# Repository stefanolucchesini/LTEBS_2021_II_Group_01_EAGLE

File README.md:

# LTEBS_2021_II_Group_01_EAGLE

This is the first assignment of electronic technologies and biosensors LAB. 

We are group 1:
*Stefano Lucchesini
*Michele Civitavecchia

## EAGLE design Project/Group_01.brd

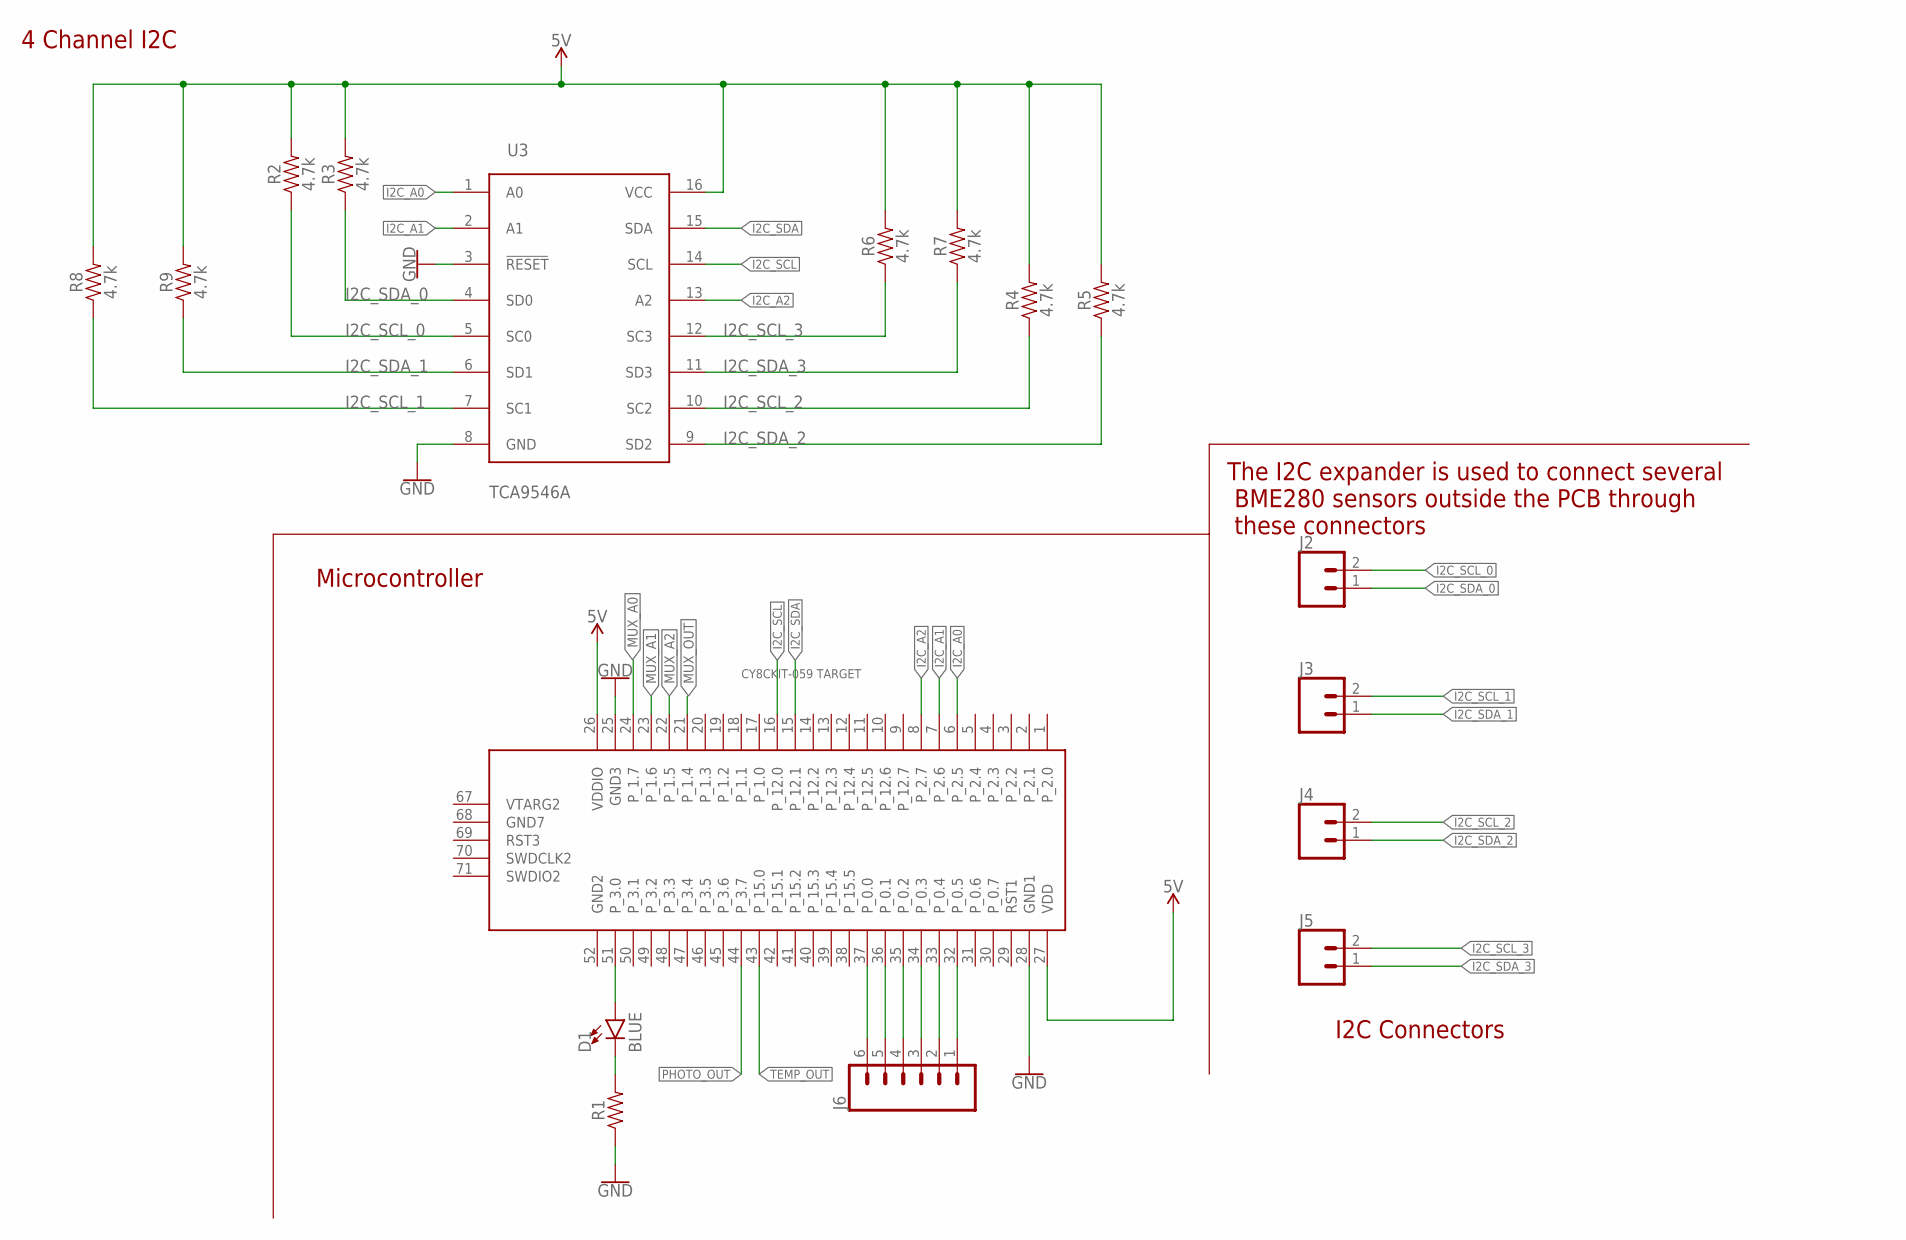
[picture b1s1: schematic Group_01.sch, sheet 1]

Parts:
D1: BLUE; LED-1206
J2, J3, J4, J5: CONN_02; 1X02
J6: CONN_06LOCK; 1X06_LOCK
R1: AXIAL-0.3
R2, R3, R4, R5, R6, R7, R8, R9: 4.7k; 0603
U3: TCA9546A; TSSOP16
U$2: CY8CKIT-059_TARGET

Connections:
5V: R2.2, R3.2, R4.2, R5.2, R6.2, R7.2, R8.2, R9.2, U3.16 (VCC), U$2.26 (VDDIO), U$2.27 (VDD); also elsewhere on the board
GND: R1.P$1 (1), U3.3 (!RESET!), U3.8 (GND), U$2.25 (GND3), U$2.28 (GND1); also elsewhere on the board
I2C_A0: U3.1 (A0), U$2.6 (P_2.5)
I2C_A1: U3.2 (A1), U$2.7 (P_2.6)
I2C_A2: U3.13 (A2), U$2.8 (P_2.7)
I2C_SCL: U3.14 (SCL), U$2.16 (P_12.0)
I2C_SCL_0: J2.2, R2.1, U3.5 (SC0)
I2C_SCL_1: J3.2, R8.1, U3.7 (SC1)
I2C_SCL_2: J4.2, R4.1, U3.10 (SC2)
I2C_SCL_3: J5.2, R6.1, U3.12 (SC3)
I2C_SDA: U3.15 (SDA), U$2.15 (P_12.1)
I2C_SDA_0: J2.1, R3.1, U3.4 (SD0)
I2C_SDA_1: J3.1, R9.1, U3.6 (SD1)
I2C_SDA_2: J4.1, R5.1, U3.9 (SD2)
I2C_SDA_3: J5.1, R7.1, U3.11 (SD3)
MUX_A0: U$2.24 (P_1.7); also elsewhere on the board
MUX_A1: U$2.23 (P_1.6); also elsewhere on the board
MUX_A2: U$2.22 (P_1.5); also elsewhere on the board
MUX_OUT: U$2.21 (P_1.4); also elsewhere on the board
unnamed: D1.A, U$2.51 (P_3.0)
unnamed: D1.C, R1.P$2 (2)
PHOTO_OUT: U$2.44 (P_3.7); also elsewhere on the board
P_0.0: J6.6, U$2.37 (P_0.0)
P_0.1: J6.5, U$2.36 (P_0.1)
P_0.2: J6.4, U$2.35 (P_0.2)
P_0.3: J6.3, U$2.34 (P_0.3)
P_0.4: J6.2, U$2.33 (P_0.4)
P_0.5: J6.1, U$2.32 (P_0.5)
TEMP_OUT: U$2.43 (P_15.0); also elsewhere on the board

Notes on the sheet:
I2C Connectors
The I2C expander is used to connect several BME280 sensors outside the PCB through these connectors
4 Channel I2C
Microcontroller

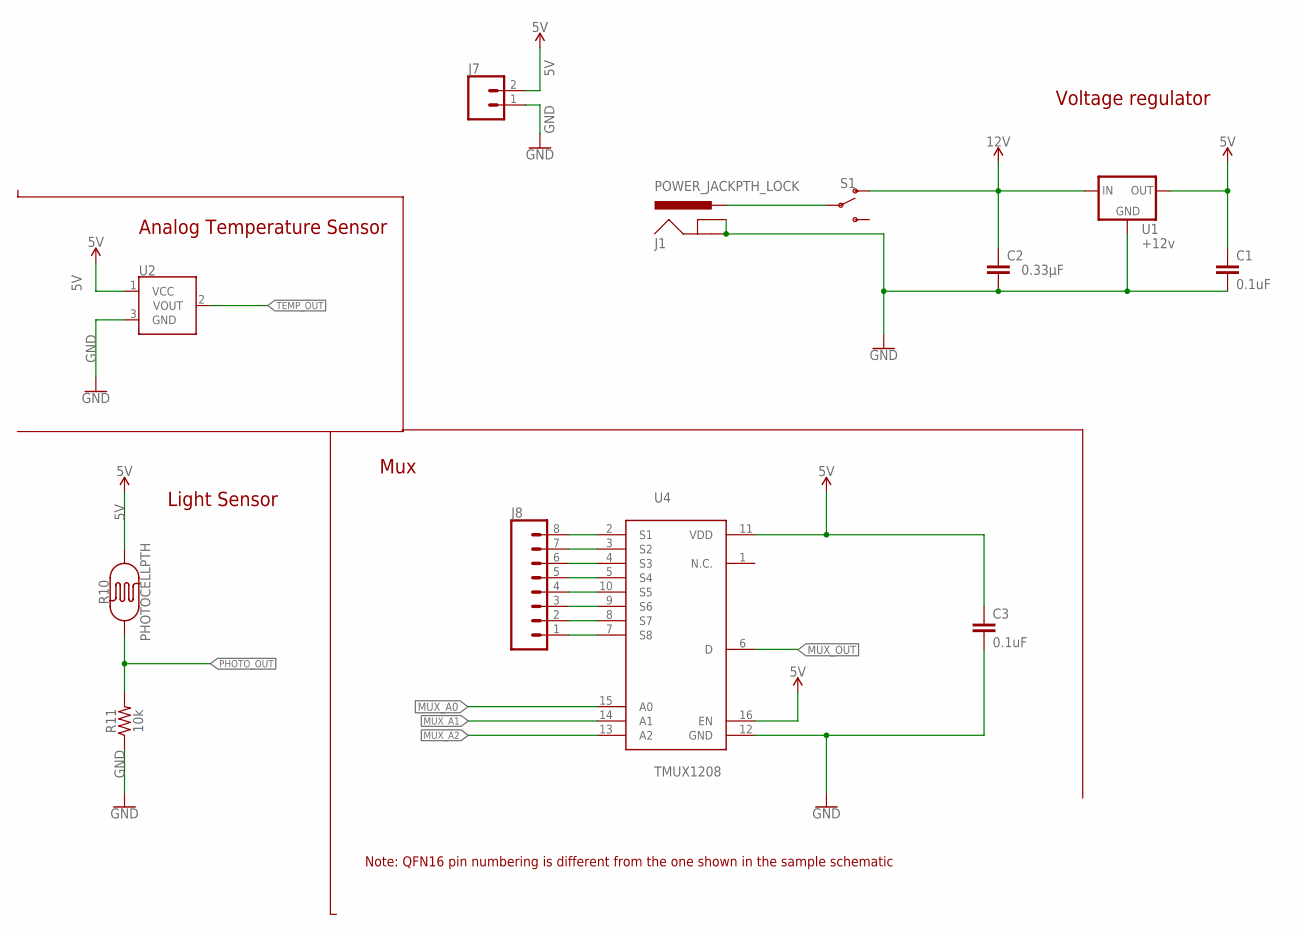
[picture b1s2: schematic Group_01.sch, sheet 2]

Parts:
C1, C3: 0.1uF; CAP-PTH-SMALL-KIT
C2: 0.33µF; 0805
J1: POWER_JACKPTH_LOCK; POWER_JACK_PTH_LOCK
J7: CONN_02; 1X02
J8: CONN_08LOCK; 1X08_LOCK
R10: PHOTOCELLPTH; PHOTOCELL
R11: 10k; 0603
S1: SWITCH-SPDT-PTH-11.6X4.0MM; SWITCH_SPDT_PTH_11.6X4.0MM
U1: +12v; TO-252
U2: TMP36GT9; TO-92
U4: TMUX1208; QFN16

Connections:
5V: C1.1, C3.1, J7.2, R10.2, U1.2 (OUT), U2.1 (VCC), U4.11 (VDD), U4.16 (EN); also elsewhere on the board
12V: C2.1, S1.1 (O), U1.1 (IN)
GND: C1.2, C2.2, C3.2, J1.GND, J1.GNDBREAK, J7.1, R11.1, U1.3 (GND), U2.3 (GND), U4.12 (GND); also elsewhere on the board
MUX_A0: U4.15 (A0); also elsewhere on the board
MUX_A1: U4.14 (A1); also elsewhere on the board
MUX_A2: U4.13 (A2); also elsewhere on the board
MUX_OUT: U4.6 (D); also elsewhere on the board
PHOTO_OUT: R10.1, R11.2; also elsewhere on the board
S1: J8.8, U4.2 (S1)
S2: J8.7, U4.3 (S2)
S3: J8.6, U4.4 (S3)
S4: J8.5, U4.5 (S4)
S5: J8.4, U4.10 (S5)
S6: J8.3, U4.9 (S6)
S7: J8.2, U4.8 (S7)
S8: J8.1, U4.7 (S8)
SWITCH: J1.PWR, S1.2
TEMP_OUT: U2.2 (VOUT); also elsewhere on the board

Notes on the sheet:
Analog Temperature Sensor
Light Sensor
Voltage regulator
Mux
Note: QFN16 pin numbering is different from the one shown in the sample schematic

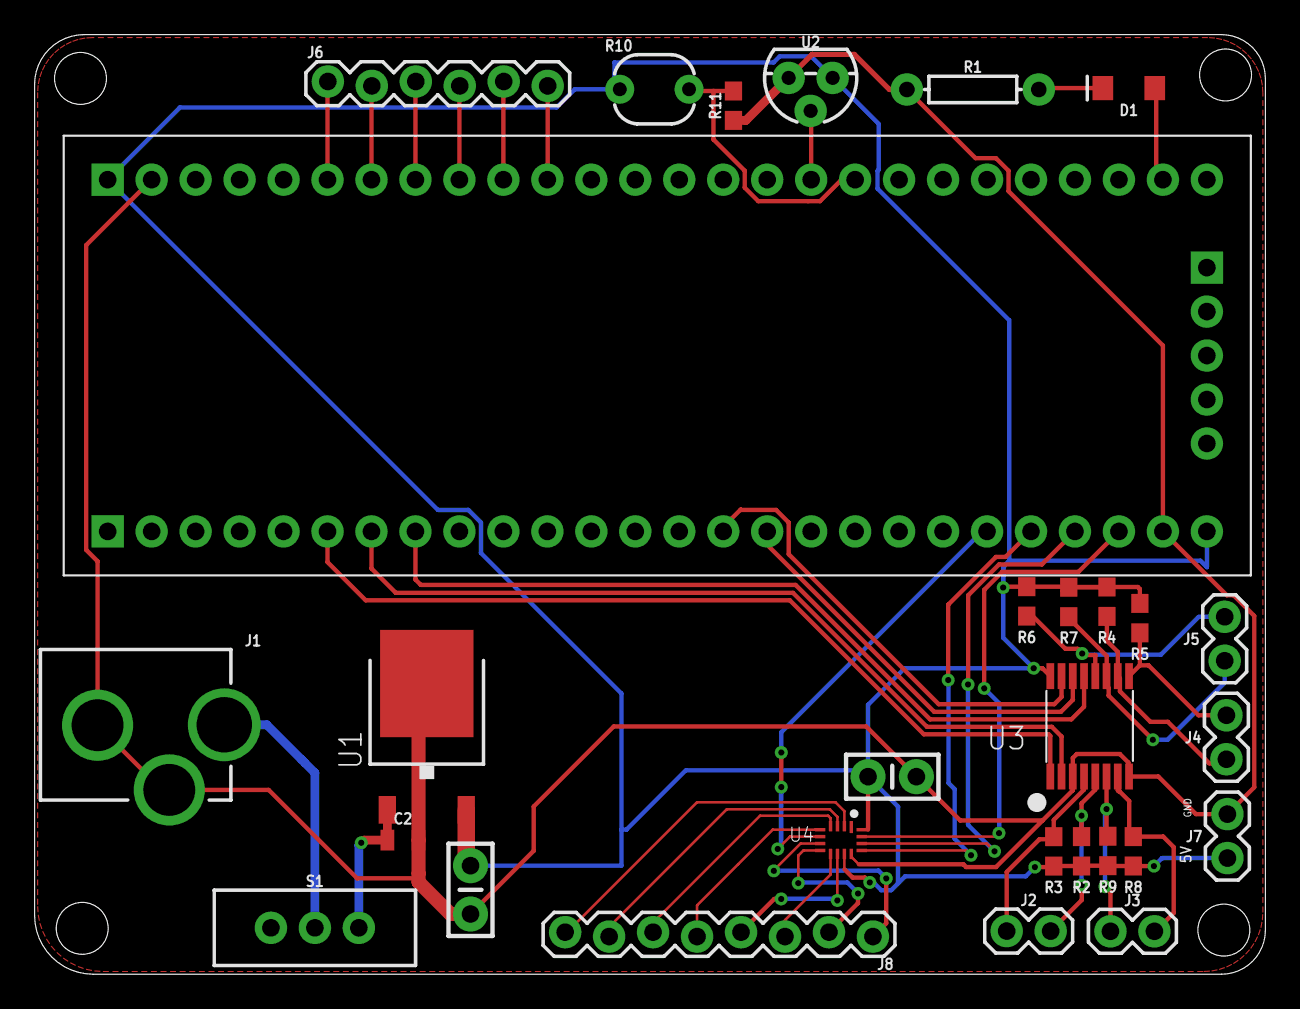
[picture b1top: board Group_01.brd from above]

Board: 2 copper layers, 71.1 x 54.3 mm, 29 parts (0 on the bottom side), 39 nets.

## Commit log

2021-03-18 Primo commit
2021-03-18 Aggiunto file libreria vuoto
2021-03-18 QFN16 Component footprint added
    QFN16 Component footprint added
2021-03-18 Added QFN16 symbol and package
2021-03-18 Added i2c device (description to do)
2021-03-18 Created .gitignore
    Useful to avoid useless eagle files
2021-03-18 Added all components to schematics
2021-03-18 Schematics changes
2021-03-18 Added description to TCA9546A
    And small edit to device and package name
2021-03-18 Delete eagle.epf
    File which doesn't need to be tracked
2021-03-19 Schematic update
    Microcontroller, TCA and connectors all connected
2021-03-19 Changed QFN16 and finished schematics
2021-03-20 Added comments on schematic, board layout, dru file
    The board still needs to be routed
2021-03-22 Routed board
    Partially
2021-03-22 Added Description for TMUX
2021-03-22 Some routing improvements
    GND and 5V planes added
2021-03-23 Trace width for mux reduced to 6 mils
    Board complete, no drc, erc errors
2021-03-24 changed position of jumpers
2021-03-24 Changed pin name in QFN16
2021-03-25 Silkscreen improved
    It's the tname layer
2021-03-25 5V on bottom and GND on top
    Corrected, it was the opposite before!!
2021-03-25 Schematic on 2 sheets
    And other minor improvements on the board, added readme file
2021-03-25 Changed name
2021-03-25 Revert "Changed name"
    This reverts commit 609342ddda2755176251b6021189b0587eea2b8d.
2021-03-25 Added measure in board
2021-03-26 Fixed connection between mux and microcontroller
2021-03-26 Final Version

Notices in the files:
parts and their libraries:
SparkFun-Connectors: Licensing: Creative Commons ShareAlike 4.0 International - https://creativecommons.org/licenses/by-sa/4.0
